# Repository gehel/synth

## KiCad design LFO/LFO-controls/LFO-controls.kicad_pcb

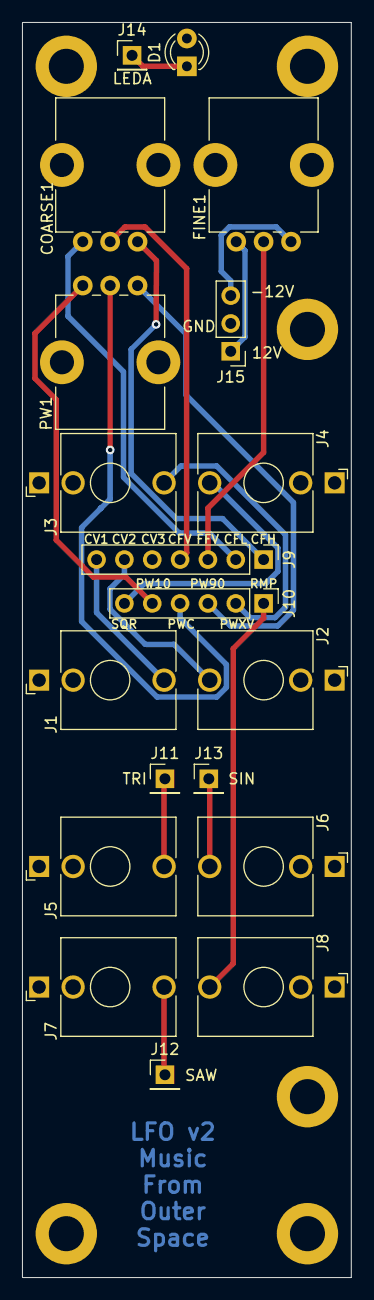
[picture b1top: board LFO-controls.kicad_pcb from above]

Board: 2 copper layers, 30.0 x 114.5 mm, 25 parts (0 on the bottom side), 19 nets.

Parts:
COARSE1: R_Potentiometer; Potentiometer_Bourns_PTV09A-1_Single_Vertical
D1: LED; LED_D3.0mm
FINE1: R_Potentiometer; Potentiometer_Bourns_PTV09A-1_Single_Vertical
H1, H2, H3, H4, H5, H6: MountingHole_Pad; MountingHole_3.2mm_M3_DIN965_Pad
J1, J2, J3, J4, J5, J6, J7, J8: AudioJack2; Jack_3.5mm_QingPu_WQP-PJ398SM_Vertical_CircularHoles
J9: Conn_01x06; PinHeader_1x07_P2.54mm_Vertical
J10: Conn_01x06; PinHeader_1x06_P2.54mm_Vertical
J11, J12, J13, J14: Conn_01x01; PinHeader_1x01_P2.54mm_Vertical
J15: Conn_01x03; PinHeader_1x03_P2.54mm_Vertical
PW1: R_Potentiometer; Potentiometer_Bourns_PTV09A-1_Single_Vertical

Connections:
+12V: FINE1.3, J15.1
-12V: FINE1.1, J15.3
CFH: COARSE1.1, J9.1
CFL: COARSE1.3, J9.2
CFV: COARSE1.2, J9.4
CV1: J1.T, J9.7
CV2: J2.T, J9.6
FFV: FINE1.2, J9.3
GND: D1.2 (A), H1.1, H2.1, H3.1, H4.1, H5.1, H6.1, J1.S, J2.S, J3.S, J4.S, J5.S, J6.S, J7.S, J8.S, J15.2
LEDA: D1.1 (K), J14.1
PW10: J10.5, PW1.1
PW90: J10.3, PW1.3
PWC: J10.4, PW1.2
PWXV: J3.T, J10.2
RMP: J8.T, J10.1
SAW: J7.T, J12.1
SIN: J6.T, J13.1
SQR: J4.T, J10.6
TRI: J5.T, J11.1

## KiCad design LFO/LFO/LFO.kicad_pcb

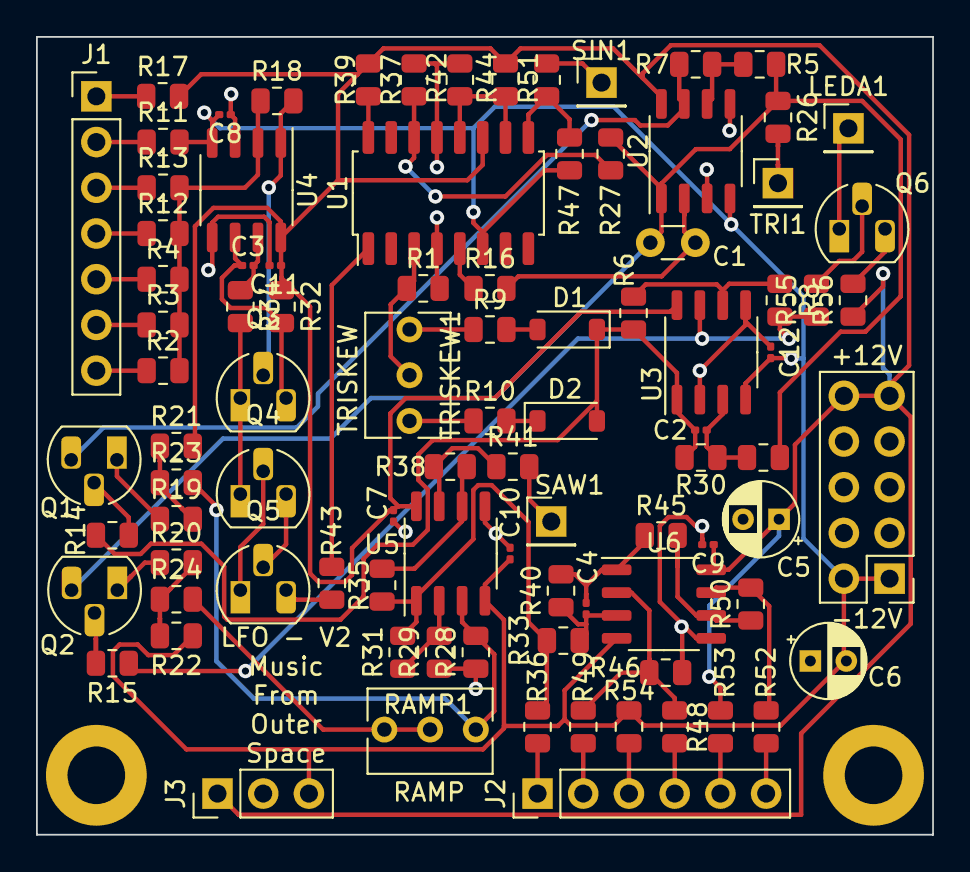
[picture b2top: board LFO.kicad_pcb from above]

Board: 2 copper layers, 49.8 x 44.3 mm, 94 parts (0 on the bottom side), 65 nets.

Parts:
C1: 20nF; C_Disc_D3.0mm_W1.6mm_P2.50mm
C2, C4: 10pF; C_0201_0603Metric
C3: 100pF; C_0201_0603Metric
C5, C6: 10uF; CP_Radial_D4.0mm_P2.00mm
C7, C8, C9, C10, C11, C12: 100nF; C_0201_0603Metric
D1, D2: 1N914; D_SOD-123
H1, H2: MountingHole_Pad; MountingHole_3.2mm_M3_DIN965_Pad
J1: Conn_01x06; PinHeader_1x07_P2.54mm_Vertical
J2: Conn_01x06; PinHeader_1x06_P2.54mm_Vertical
J3: Conn_01x03; PinHeader_1x03_P2.54mm_Vertical
J4: Conn_02x05_Odd_Even; PinHeader_2x05_P2.54mm_Vertical
LEDA1: Conn_01x01; PinHeader_1x01_P2.54mm_Vertical
Q1, Q2: NJFET; TO-92_HandSolder
Q3, Q4, Q6: 2N3904; TO-92_HandSolder
Q5: 2N3906; TO-92_HandSolder
R1, R36, R41: 1K; R_0805_2012Metric
R2, R3, R4, R9, R10, R12, R26, R31, R33, R53, R54, R55: 100K; R_0805_2012Metric
R5, R7: 20K; R_0805_2012Metric
R6, R8, R29: 47K; R_0805_2012Metric
R11, R18, R32, R47, R51, R56: 4.7K; R_0805_2012Metric
R13: 3M; R_0805_2012Metric
R14, R15: 30K; R_0805_2012Metric
R16: 39K; R_0805_2012Metric
R17, R45: 27K; R_0805_2012Metric
R19, R20, R23, R28, R34, R35, R38, R43, R48, R49, R50, R52: 10K; R_0805_2012Metric
R21, R22: 15K; R_0805_2012Metric
R24: 9.1K; R_0805_2012Metric
R25: 120K; R_0805_2012Metric
R27: 110K; R_0805_2012Metric
R30: 270K; R_0805_2012Metric
R37: 2K; R_0805_2012Metric
R39, R42: 180K; R_0805_2012Metric
R40: 4.7M; R_0805_2012Metric
R44: 2M; R_0805_2012Metric
R46: 1M; R_0805_2012Metric
RAMP1: 2K; Potentiometer_Bourns_3266Y_Vertical
SAW1: Conn_01x01; PinHeader_1x01_P2.54mm_Vertical
SIN1: Conn_01x01; PinHeader_1x01_P2.54mm_Vertical
TRI1: Conn_01x01; PinHeader_1x01_P2.54mm_Vertical
TRISKEW1: 100K; Potentiometer_Bourns_3266Y_Vertical
U1: LM13700; SOP-16_4.4x10.4mm_P1.27mm
U2, U3, U5, U6: TL082; SOP-8_3.9x4.9mm_P1.27mm
U4: TL072; SOP-8_3.9x4.9mm_P1.27mm

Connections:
+12V: C5.1, C7.1, C9.1, C11.1, J3.1, J4.9, J4.10, R17.2, R21.2, R32.1, R39.1, R44.2, R53.1, R56.1, U1.11 (V+), U2.8 (V+), U3.8 (V+), U4.8 (V+), U5.8 (V+), U6.8 (V+)
-12V: C6.2, C8.2, C10.2, C12.2, J3.3, J4.1, J4.2, R11.2, R22.1, R47.2, R54.2, U1.6 (V-), U2.4 (V-), U3.4 (V-), U4.4 (V-), U5.4 (V-), U6.4 (V-)
CFH: J1.1, R17.1
CFL: J1.2, R11.1
CFV: J1.4, R12.1
CV1: J1.7, R2.1
CV2: J1.6, R3.1
CV3: J1.5, R4.1
FFV: J1.3, R13.1
GND: C5.2, C6.1, C7.2, C8.1, C9.2, C10.1, C11.2, C12.1, H1.1, H2.1, J3.2, J4.3, J4.4, J4.5, J4.6, J4.7, J4.8, Q4.2 (B), Q5.1 (E), R1.2, R28.1, R29.1, R37.1, R42.1, R46.1, U1.4 (-), U1.13 (-), U2.3 (+), U2.5 (+), U3.2 (-), U3.5 (+), U4.3 (+), U4.5 (+), U5.5 (+), U6.5 (+)
LEDA: LEDA1.1, Q6.1 (E)
unnamed: C3.2, R34.1, U4.7
unnamed: C4.2, R40.2, R45.1, U6.1
unnamed: D1.2 (A), R9.2
unnamed: C2.2, D1.1 (K), D2.2 (A), R6.1, R14.1, R30.2, U3.1
unnamed: D2.1 (K), R10.2
unnamed: Q1.1 (D), R19.1
unnamed: Q1.2 (G), R14.2
unnamed: Q1.3 (S), R7.2, U2.7
unnamed: Q2.1 (D), R20.1
unnamed: Q2.2 (G), R15.2
unnamed: C1.2, Q2.3 (S), R5.1, R25.1, R26.1, R27.1, U2.1
unnamed: Q3.2 (B), R18.2, U4.1
unnamed: C3.1, Q3.3 (C), R32.2, U4.6 (-)
unnamed: Q3.1 (E), Q4.1 (E), R34.2
unnamed: Q4.3 (C), Q5.2 (B)
unnamed: Q5.3 (C), R43.1
unnamed: Q6.2 (B), R55.2
unnamed: Q6.3 (C), R56.2
unnamed: R9.1, TRISKEW1.3
unnamed: R10.1, TRISKEW1.1
unnamed: R16.1, U1.5
unnamed: R19.2, R21.1, R23.1
unnamed: R20.2, R22.2, R24.1
unnamed: R24.2, RAMP1.2, RAMP1.3
unnamed: R31.2, R33.1, R35.1, R36.1, U5.1
unnamed: R38.2, R41.1, U5.7
unnamed: R39.2, U1.16
unnamed: R42.2, R44.1, U1.10, U1.12
unnamed: R43.2, U1.1
unnamed: R47.1, R51.1, U1.9
unnamed: R50.2, R52.1, U6.7
unnamed: R27.2, R37.2, U1.14 (+)
unnamed: R1.1, TRISKEW1.2, U1.3 (+)
unnamed: C1.1, R16.2, U2.2 (-)
unnamed: R5.2, R7.1, U2.6 (-)
unnamed: C2.1, R25.2, R30.1, U3.3 (+)
unnamed: R6.2, R8.1, U3.6 (-)
unnamed: R2.2, R3.2, R4.2, R12.2, R13.2, R18.1, U4.2 (-)
unnamed: R23.2, R28.2, RAMP1.1, U5.3 (+)
unnamed: R29.2, R31.1, U5.2 (-)
unnamed: R35.2, R38.1, U5.6 (-)
unnamed: C4.1, R33.2, R40.1, U6.3 (+)
unnamed: R46.2, R48.1, R49.1, U6.2 (-)
unnamed: R45.2, R50.1, U6.6 (-)
PW10: J2.5, R53.2
PW90: J2.3, R54.1
PWC: J2.4, R48.2
PWXV: J2.2, R49.2
RMP: J2.1, R36.2
SAW: R41.2, SAW1.1
SIN: R51.2, SIN1.1
SQR: J2.6, R52.2
TRI: R26.2, TRI1.1
ZZ: R8.2, R15.1, R55.1, U3.7

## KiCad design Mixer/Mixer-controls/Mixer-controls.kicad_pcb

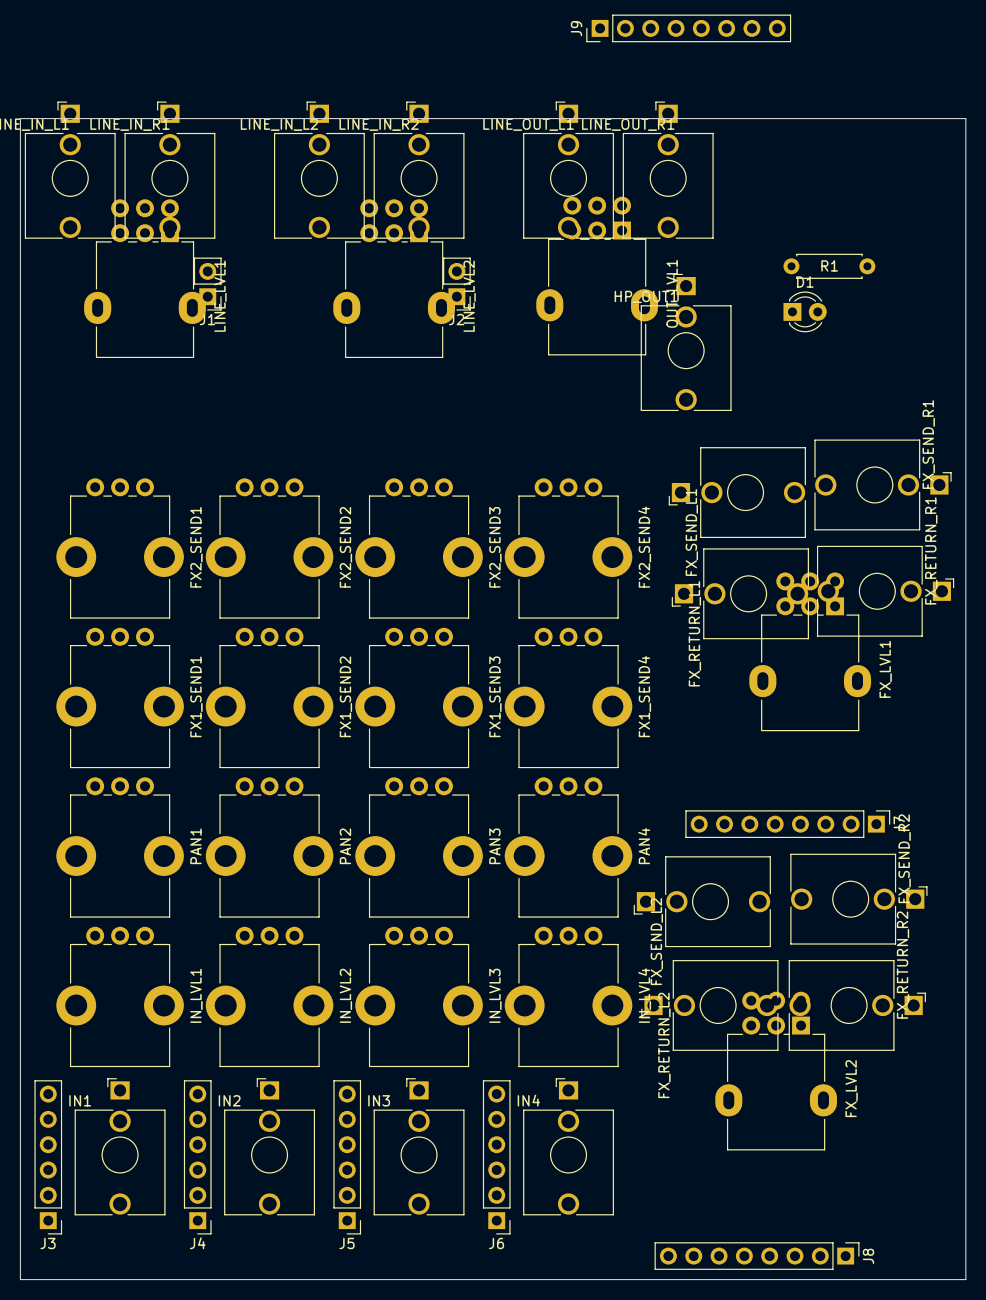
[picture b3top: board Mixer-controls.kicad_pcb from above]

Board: 2 copper layers, 94.9 x 116.5 mm, 51 parts (0 on the bottom side), 45 nets, no tracks yet.

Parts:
D1: LED; LED_D3.0mm
FX1_SEND1, FX1_SEND2, FX1_SEND3, FX1_SEND4, FX2_SEND1, FX2_SEND2, FX2_SEND3, FX2_SEND4: 100K; Potentiometer_Bourns_PTV09A-1_Single_Vertical
FX_LVL1, FX_LVL2: 100K; Potentiometer_Alpha_RD902F-40-00D_Dual_Vertical
FX_RETURN_L1, FX_RETURN_L2: AudioJack3; Jack_3.5mm_QingPu_WQP-PJ398SM_Vertical_CircularHoles
FX_RETURN_R1, FX_RETURN_R2: AudioJack3; Jack_3.5mm_QingPu_WQP-PJ398SM_Vertical_CircularHoles
FX_SEND_L1, FX_SEND_L2: AudioJack3; Jack_3.5mm_QingPu_WQP-PJ398SM_Vertical_CircularHoles
FX_SEND_R1, FX_SEND_R2: AudioJack3; Jack_3.5mm_QingPu_WQP-PJ398SM_Vertical_CircularHoles
HP_OUT1: AudioJack3; Jack_3.5mm_QingPu_WQP-PJ398SM_Vertical_CircularHoles
IN1, IN2, IN3, IN4: AudioJack3; Jack_3.5mm_QingPu_WQP-PJ398SM_Vertical_CircularHoles
IN_LVL1, IN_LVL2, IN_LVL3, IN_LVL4: 100K; Potentiometer_Bourns_PTV09A-1_Single_Vertical
J1, J2: Conn_01x02; PinHeader_1x02_P2.54mm_Vertical
J3, J4, J5, J6: Conn_01x06; PinHeader_1x06_P2.54mm_Vertical
J7, J8, J9: Conn_01x08; PinHeader_1x08_P2.54mm_Vertical
LINE_IN_L1, LINE_IN_L2: AudioJack3; Jack_3.5mm_QingPu_WQP-PJ398SM_Vertical_CircularHoles
LINE_IN_R1, LINE_IN_R2: AudioJack3; Jack_3.5mm_QingPu_WQP-PJ398SM_Vertical_CircularHoles
LINE_LVL1, LINE_LVL2: 100K; Potentiometer_Alpha_RD902F-40-00D_Dual_Vertical
LINE_OUT_L1: AudioJack3; Jack_3.5mm_QingPu_WQP-PJ398SM_Vertical_CircularHoles
LINE_OUT_R1: AudioJack3; Jack_3.5mm_QingPu_WQP-PJ398SM_Vertical_CircularHoles
OUT_LVL1: 100K; Potentiometer_Alpha_RD902F-40-00D_Dual_Vertical
PAN1, PAN2, PAN3, PAN4: 100K; Potentiometer_Bourns_PTV09A-1_Single_Vertical
R1: 4.7K; R_Axial_DIN0207_L6.3mm_D2.5mm_P7.62mm_Horizontal

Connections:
/channel1/E1: FX1_SEND1.2, J3.5
/channel1/E2: FX2_SEND1.2, J3.6
/channel1/EF: FX1_SEND1.3, FX2_SEND1.3, J3.4
/channel1/IN: IN_LVL1.2, J3.1
/channel1/PANL: J3.2, PAN1.1
/channel1/PANR: J3.3, PAN1.3
/channel2/E1: FX1_SEND2.2, J4.5
/channel2/E2: FX2_SEND2.2, J4.6
/channel2/EF: FX1_SEND2.3, FX2_SEND2.3, J4.4
/channel2/IN: IN_LVL2.2, J4.1
/channel2/PANL: J4.2, PAN2.1
/channel2/PANR: J4.3, PAN2.3
/channel3/E1: FX1_SEND3.2, J5.5
/channel3/E2: FX2_SEND3.2, J5.6
/channel3/EF: FX1_SEND3.3, FX2_SEND3.3, J5.4
/channel3/IN: IN_LVL3.2, J5.1
/channel3/PANL: J5.2, PAN3.1
/channel3/PANR: J5.3, PAN3.3
/channel4/E1: FX1_SEND4.2, J6.5
/channel4/E2: FX2_SEND4.2, J6.6
/channel4/EF: FX1_SEND4.3, FX2_SEND4.3, J6.4
/channel4/IN: IN_LVL4.2, J6.1
/channel4/PANL: J6.2, PAN4.1
/channel4/PANR: J6.3, PAN4.3
/outputs/HPHR: HP_OUT1.T, J9.7
/outputs/HPIL: J9.1, OUT_LVL1.2
/outputs/HPIR: J9.8, OUT_LVL1.5
/outputs/HPOL: J9.3, OUT_LVL1.3
/outputs/HPOR: J9.6, OUT_LVL1.6
/outputs/LLOUT: J9.4, LINE_OUT_R1.T
/outputs/RLOUT: J9.5, LINE_OUT_L1.T
GND: FX1_SEND1.1, FX1_SEND1.MP (MountPin), FX1_SEND2.1, FX1_SEND2.MP (MountPin), FX1_SEND3.1, FX1_SEND3.MP (MountPin), FX1_SEND4.1, FX1_SEND4.MP (MountPin), FX2_SEND1.1, FX2_SEND1.MP (MountPin), FX2_SEND2.1, FX2_SEND2.MP (MountPin), FX2_SEND3.1, FX2_SEND3.MP (MountPin), FX2_SEND4.1, FX2_SEND4.MP (MountPin), FX_RETURN_L1.S, FX_RETURN_L2.S, FX_RETURN_R1.S, FX_RETURN_R2.S, FX_SEND_L1.S, FX_SEND_L2.S, FX_SEND_R1.S, FX_SEND_R2.S, HP_OUT1.S, IN1.S, IN2.S, IN3.S, IN4.S, IN_LVL1.1, IN_LVL1.MP (MountPin), IN_LVL2.1, IN_LVL2.MP (MountPin), IN_LVL3.1, IN_LVL3.MP (MountPin), IN_LVL4.1, IN_LVL4.MP (MountPin), LINE_IN_L1.S, LINE_IN_L2.S, LINE_IN_R1.S, LINE_IN_R2.S, LINE_LVL1.1, LINE_LVL1.4, LINE_LVL2.1, LINE_LVL2.4, LINE_OUT_L1.S, LINE_OUT_R1.S, OUT_LVL1.1, OUT_LVL1.4, PAN1.2, PAN1.MP (MountPin), PAN2.2, PAN2.MP (MountPin), PAN3.2, PAN3.MP (MountPin), PAN4.2, PAN4.MP (MountPin), R1.2
unnamed: D1.1 (K), R1.1
unnamed: IN1.T, IN_LVL1.3
unnamed: IN2.T, IN_LVL2.3
unnamed: IN3.T, IN_LVL3.3
unnamed: IN4.T, IN_LVL4.3
unnamed: J1.1, LINE_LVL1.2
unnamed: J1.2, LINE_LVL1.5
unnamed: J2.1, LINE_LVL2.2
unnamed: J2.2, LINE_LVL2.5
unnamed: LINE_IN_L1.T, LINE_LVL1.3
unnamed: LINE_IN_L2.T, LINE_LVL2.3
unnamed: LINE_IN_R1.T, LINE_LVL1.6
unnamed: LINE_IN_R2.T, LINE_LVL2.6

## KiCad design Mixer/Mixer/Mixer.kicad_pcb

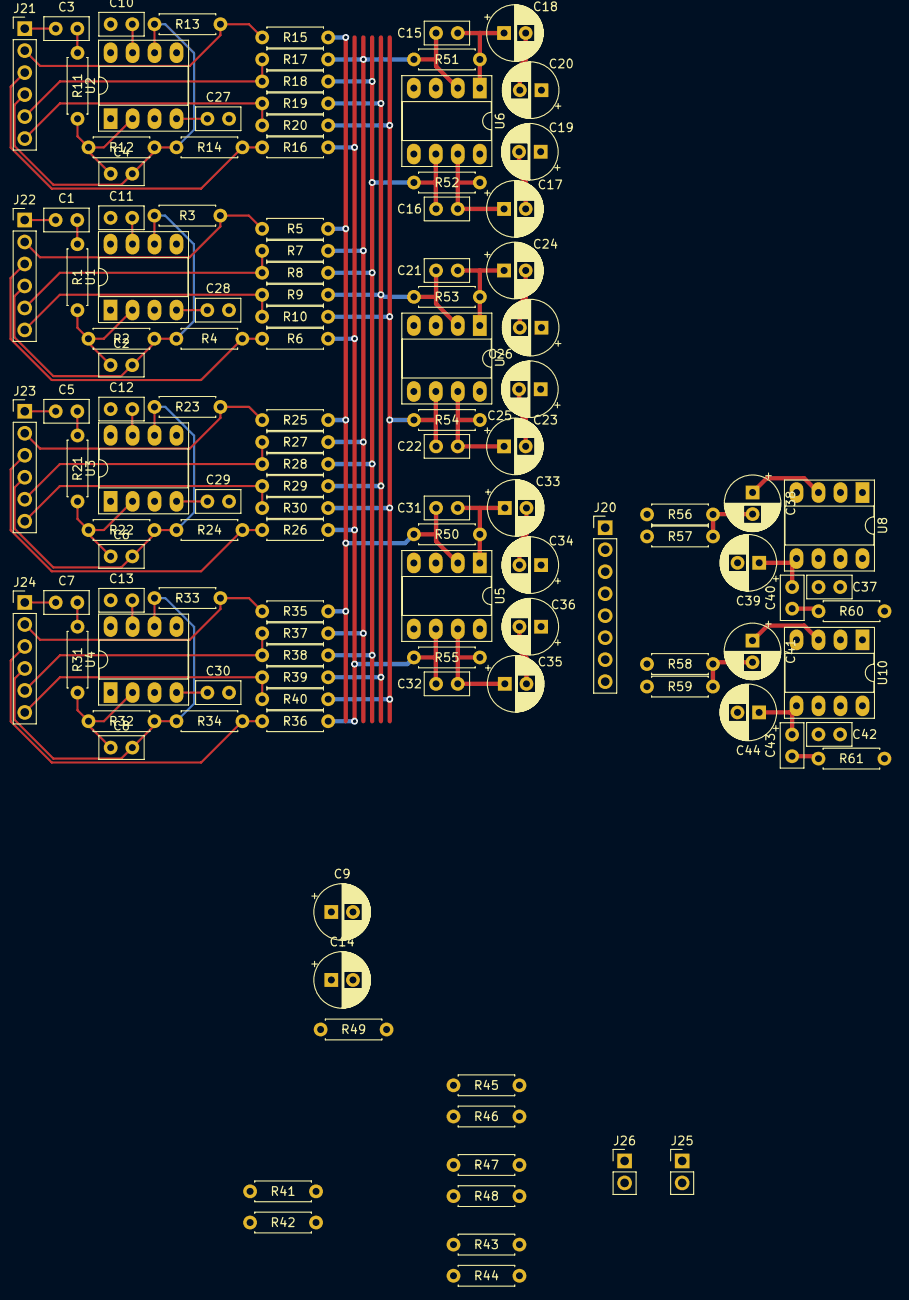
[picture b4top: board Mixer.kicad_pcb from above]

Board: 2 copper layers, 121 parts (0 on the bottom side), 71 nets.

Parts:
C1, C3, C5, C7, C10, C11, C12, C13, C27, C28, C29, C30, C37, C42: 100nF; C_Disc_D5.0mm_W2.5mm_P2.50mm
C2, C4, C6, C8, C15, C16, C21, C22, C31, C32: 10pF; C_Disc_D5.0mm_W2.5mm_P2.50mm
C9, C14: 10uF; CP_Radial_D6.3mm_P2.50mm
C17, C18, C19, C20, C23, C24, C25, C26, C33, C34, C35, C36: 47uF; CP_Radial_D6.3mm_P2.50mm
C38, C41: 1uF; CP_Radial_D6.3mm_P2.50mm
C39, C44: 220uF; CP_Radial_D6.3mm_P2.50mm
C40, C43: 47nF; C_Disc_D5.0mm_W2.5mm_P2.50mm
J20: Conn_01x08; PinHeader_1x08_P2.54mm_Vertical
J21, J22, J23, J24: Conn_01x06; PinHeader_1x06_P2.54mm_Vertical
J25, J26: Conn_01x02; PinHeader_1x02_P2.54mm_Vertical
R1, R11, R21, R31: 47K; R_Axial_DIN0207_L6.3mm_D2.5mm_P7.62mm_Horizontal
R2, R12, R22, R32: 470K; R_Axial_DIN0207_L6.3mm_D2.5mm_P7.62mm_Horizontal
R3, R4, R5, R6, R13, R14, R15, R16, R23, R24, R25, R26, R33, R34, R35, R36, R49: 120K; R_Axial_DIN0207_L6.3mm_D2.5mm_P7.62mm_Horizontal
R7, R8, R9, R10, R17, R18, R19, R20, R27, R28, R29, R30, R37, R38, R39, R40: 20K; R_Axial_DIN0207_L6.3mm_D2.5mm_P7.62mm_Horizontal
R41, R42, R43, R44, R45, R46, R47, R48: 150K; R_Axial_DIN0207_L6.3mm_D2.5mm_P7.62mm_Horizontal
R50, R55: 300K; R_Axial_DIN0207_L6.3mm_D2.5mm_P7.62mm_Horizontal
R51, R52, R53, R54: 15K; R_Axial_DIN0207_L6.3mm_D2.5mm_P7.62mm_Horizontal
R56, R58: 100K; R_Axial_DIN0207_L6.3mm_D2.5mm_P7.62mm_Horizontal
R57, R59: 4.7K; R_Axial_DIN0207_L6.3mm_D2.5mm_P7.62mm_Horizontal
R60, R61: 10R; R_Axial_DIN0207_L6.3mm_D2.5mm_P7.62mm_Horizontal
U1, U2, U3, U4: TL071; DIP-8_W7.62mm_Socket_LongPads
U5, U6, U7: TL072; DIP-8_W7.62mm_Socket_LongPads
U8, U10: LM386; DIP-8_W7.62mm_Socket_LongPads

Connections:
+12V: C9.1, C10.2, C11.2, C12.2, C13.2, C37.2, C42.2, U1.7 (V+), U2.7 (V+), U3.7 (V+), U4.7 (V+), U5.8 (V+), U6.8 (V+), U7.8 (V+), U8.6 (V+), U10.6 (V+)
-12V: C14.2, C27.1, C28.1, C29.1, C30.1, U1.4 (V-), U2.4 (V-), U3.4 (V-), U4.4 (V-), U5.4 (V-), U6.4 (V-), U7.4 (V-)
C1E1: J21.5, R17.1, R18.1
C1E2: J21.6, R19.1, R20.1
C2E1: J22.5, R7.1, R8.1
C2E2: J22.6, R9.1, R10.1
C3E1: J23.5, R27.1, R28.1
C3E2: J23.6, R29.1, R30.1
C4E1: J24.5, R37.1, R38.1
C4E2: J24.6, R39.1, R40.1
E1LB: C15.1, R7.2, R17.2, R27.2, R37.2, R51.1, U6.2 (-)
E1RB: C16.1, R8.2, R18.2, R28.2, R38.2, R52.1, U6.6 (-)
E2LB: C21.1, R9.2, R19.2, R29.2, R39.2, R53.1, U7.2 (-)
E2RB: C22.1, R10.2, R20.2, R30.2, R40.2, R54.1, U7.6 (-)
EFCH1: C4.2, J21.4, R12.2, R13.1, R14.1, U2.6
EFCH2: C2.2, J22.4, R2.2, R3.1, R4.1, U1.6
EFCH3: C6.2, J23.4, R22.2, R23.1, R24.1, U3.6
EFCH4: C8.2, J24.4, R32.2, R33.1, R34.1, U4.6
GND: C9.2, C10.1, C11.1, C12.1, C13.1, C14.1, C27.2, C28.2, C29.2, C30.2, C37.1, C42.1, R49.1, R57.1, R59.1, R60.2, R61.2, U1.3 (+), U2.3 (+), U3.3 (+), U4.3 (+), U5.3 (+), U5.5 (+), U6.3 (+), U6.5 (+), U7.3 (+), U7.5 (+), U8.2 (-), U8.4 (GND), U10.2 (-), U10.4 (GND)
HPHL: C39.2, J20.2
HPHR: C44.2, J20.7
HPIL: J20.1, R56.1
HPIR: J20.8, R58.1
HPOL: C31.2, C33.1, J20.3, R50.2, U5.1
HPOR: C32.2, C35.1, J20.6, R55.2, U5.7
IN1: C3.1, J21.1
IN2: C1.1, J22.1
IN3: C5.1, J23.1
IN4: C7.1, J24.1
LAB: C31.1, R5.2, R15.2, R25.2, R35.2, R41.2, R43.2, R45.2, R47.2, R50.1, U5.2 (-)
LLOUT: C34.1, J20.4
unnamed: C1.2, R1.1
unnamed: C3.2, R11.1
unnamed: C5.2, R21.1
unnamed: C7.2, R31.1
unnamed: C15.2, C18.1, R51.2, U6.1
unnamed: C16.2, C17.1, R52.2, U6.7
unnamed: C17.2, C19.2
unnamed: C18.2, C20.2
unnamed: C21.2, C24.1, R53.2, U7.1
unnamed: C22.2, C23.1, R54.2, U7.7
unnamed: C23.2, C25.2
unnamed: C24.2, C26.2
unnamed: C33.2, C34.2
unnamed: C35.2, C36.2
unnamed: C38.2, R56.2, R57.2
unnamed: C39.1, C40.2, U8.5
unnamed: C40.1, R60.1
unnamed: C41.2, R58.2, R59.2
unnamed: C43.1, R61.1
unnamed: C43.2, C44.1, U10.5
unnamed: C2.1, R1.2, R2.1, U1.2 (-)
unnamed: C4.1, R11.2, R12.1, U2.2 (-)
unnamed: C6.1, R21.2, R22.1, U3.2 (-)
unnamed: C8.1, R31.2, R32.1, U4.2 (-)
unnamed: C38.1, U8.3 (+)
unnamed: C41.1, U10.3 (+)
PAN1L: J21.2, R13.2, R15.1
PAN1R: J21.3, R14.2, R16.1
PAN2L: J22.2, R3.2, R5.1
PAN2R: J22.3, R4.2, R6.1
PAN3L: J23.2, R23.2, R25.1
PAN3R: J23.3, R24.2, R26.1
PAN4L: J24.2, R33.2, R35.1
PAN4R: J24.3, R34.2, R36.1
RAB: C32.1, R6.2, R16.2, R26.2, R36.2, R42.2, R44.2, R46.2, R48.2, R55.1, U5.6 (-)
RLOUT: C36.1, J20.5
SL1L: J25.1, R47.1
SL1R: J25.2, R48.1
SL2L: J26.1, R45.1
SL2R: J26.2, R46.1

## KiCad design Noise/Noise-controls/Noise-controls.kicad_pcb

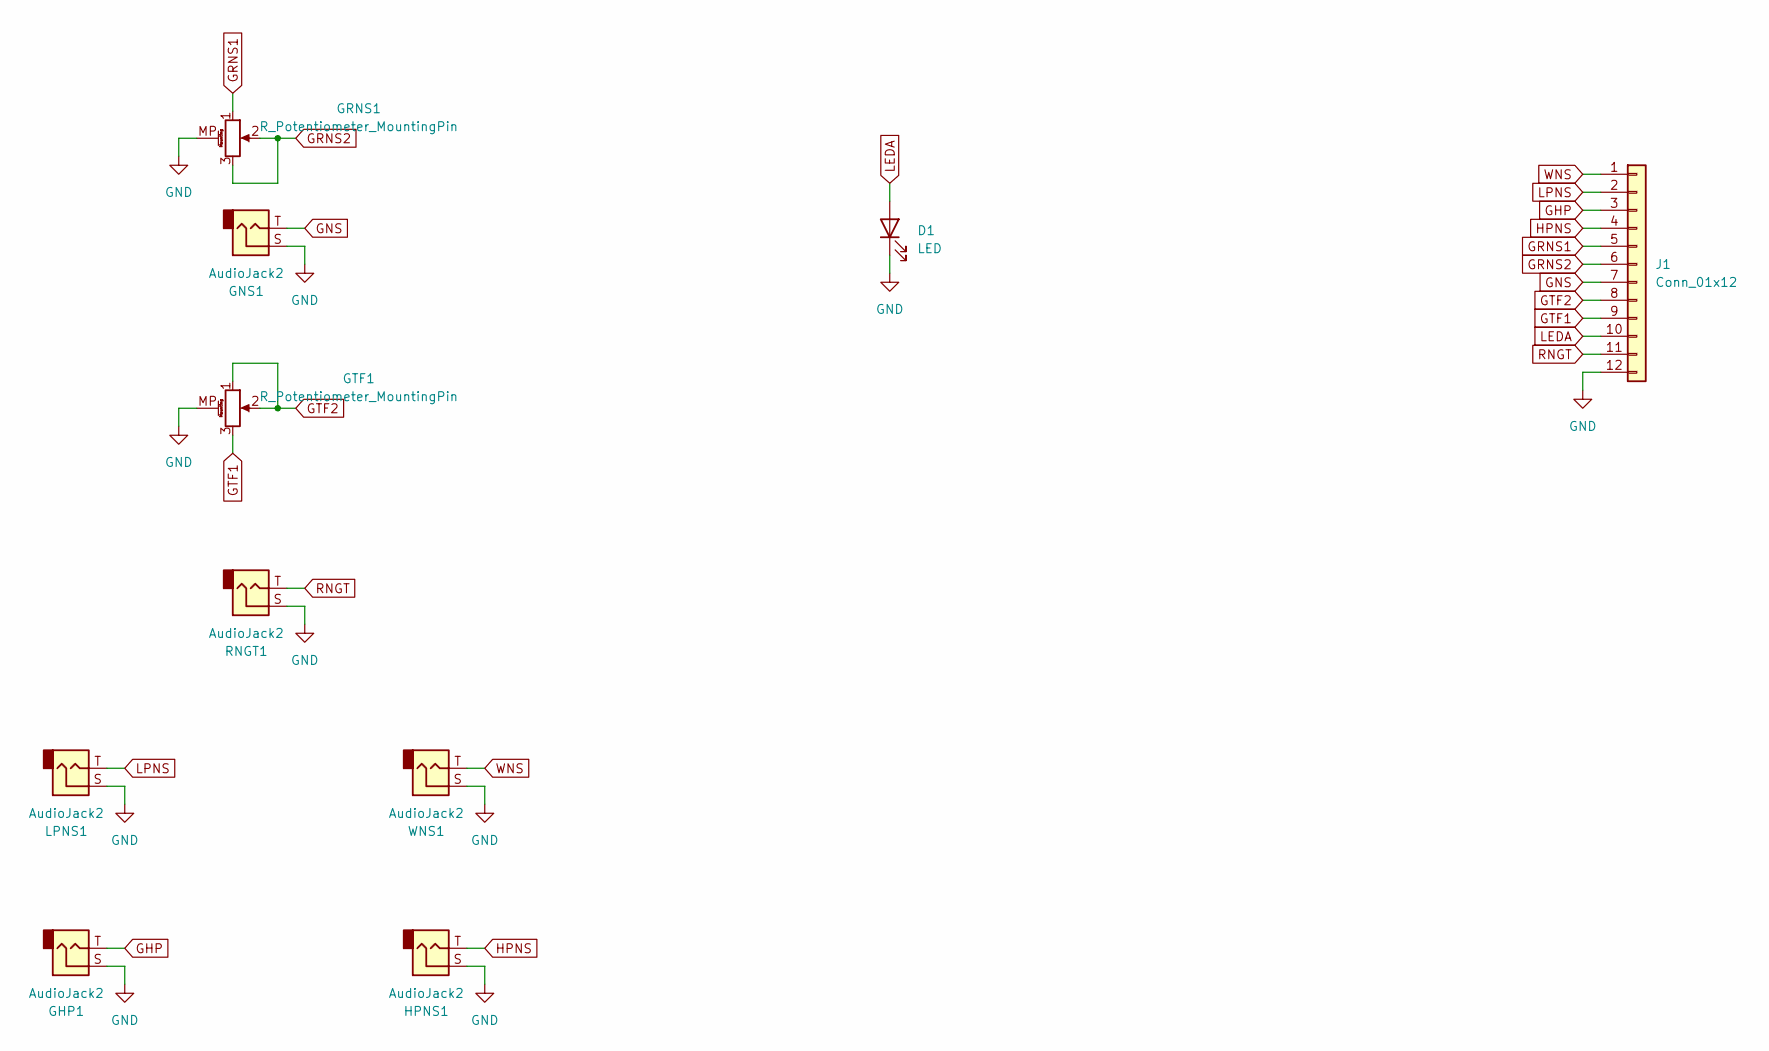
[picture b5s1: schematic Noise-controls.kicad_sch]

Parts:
D1: LED; LED_D3.0mm
GHP1: AudioJack2; Jack_3.5mm_QingPu_WQP-PJ398SM_Vertical_CircularHoles
GNS1: AudioJack2; Jack_3.5mm_QingPu_WQP-PJ398SM_Vertical_CircularHoles
GRNS1: R_Potentiometer_MountingPin; Potentiometer_Bourns_PTV09A-1_Single_Vertical
GTF1: R_Potentiometer_MountingPin; Potentiometer_Bourns_PTV09A-1_Single_Vertical
HPNS1: AudioJack2; Jack_3.5mm_QingPu_WQP-PJ398SM_Vertical_CircularHoles
J1: Conn_01x12; PinHeader_1x12_P2.54mm_Vertical
LPNS1: AudioJack2; Jack_3.5mm_QingPu_WQP-PJ398SM_Vertical_CircularHoles
RNGT1: AudioJack2; Jack_3.5mm_QingPu_WQP-PJ398SM_Vertical_CircularHoles
WNS1: AudioJack2; Jack_3.5mm_QingPu_WQP-PJ398SM_Vertical_CircularHoles

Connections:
GHP: GHP1.T, J1.3
GND: D1.1 (K), GHP1.S, GNS1.S, GRNS1.MP (MountPin), GTF1.MP (MountPin), HPNS1.S, J1.12, LPNS1.S, RNGT1.S, WNS1.S
GNS: GNS1.T, J1.7
GRNS1: GRNS1.1, J1.5
GRNS2: GRNS1.2, GRNS1.3, J1.6
GTF1: GTF1.3, J1.9
GTF2: GTF1.1, GTF1.2, J1.8
HPNS: HPNS1.T, J1.4
LEDA: D1.2 (A), J1.10
LPNS: J1.2, LPNS1.T
RNGT: J1.11, RNGT1.T
WNS: J1.1, WNS1.T

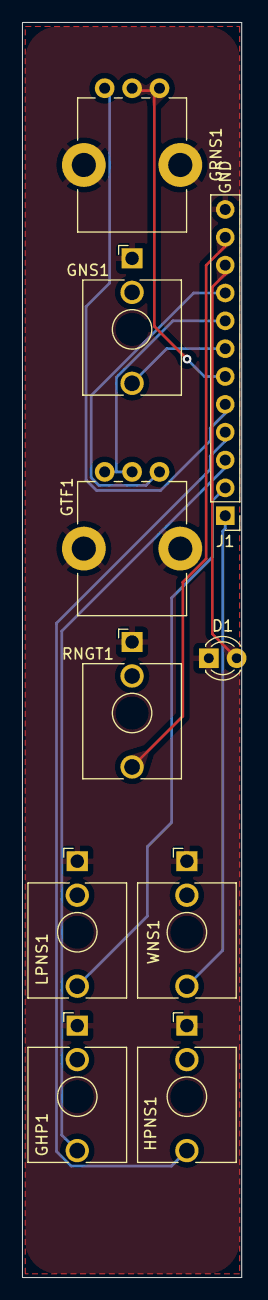
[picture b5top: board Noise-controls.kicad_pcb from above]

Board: 2 copper layers, 20.0 x 114.5 mm, 10 parts (0 on the bottom side), 12 nets.

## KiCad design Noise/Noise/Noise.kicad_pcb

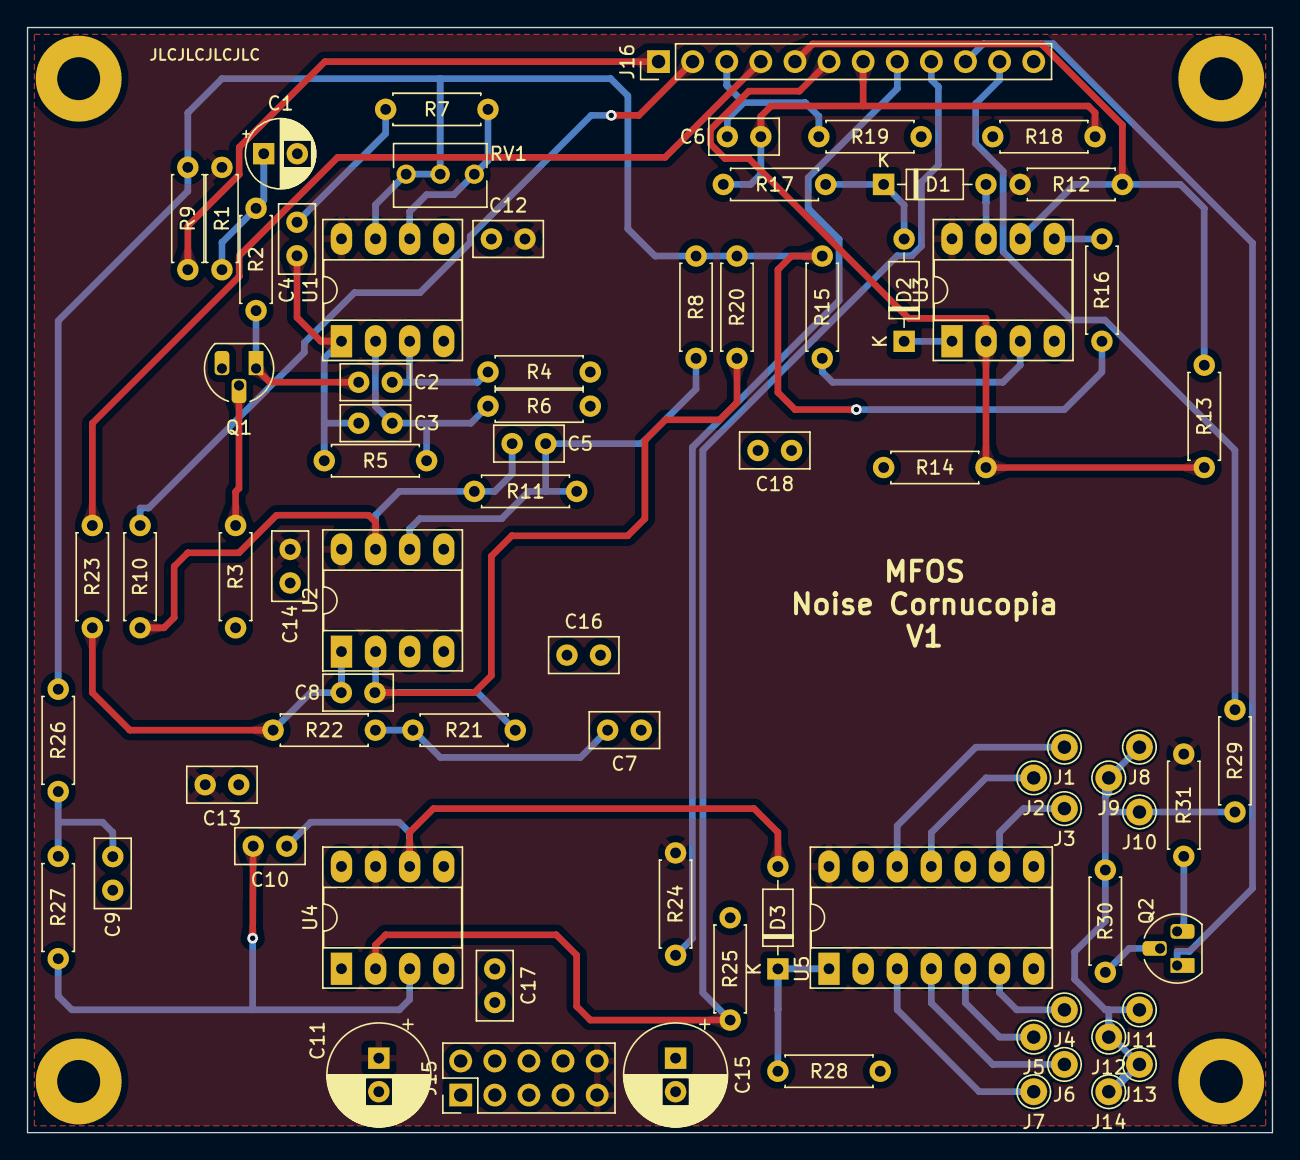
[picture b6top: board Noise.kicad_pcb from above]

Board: 4 copper layers, 92.7 x 82.3 mm, 80 parts (0 on the bottom side), 47 nets.

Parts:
C1: 1uF; CP_Radial_D5.0mm_P2.50mm
C2, C4, C12, C13, C14, C16, C17, C18: 100nF; C_Disc_D5.0mm_W2.5mm_P2.50mm
C3, C10: 10pF; C_Disc_D5.0mm_W2.5mm_P2.50mm
C5, C6: 1nF; C_Disc_D5.0mm_W2.5mm_P2.50mm
C7: 10nF; C_Disc_D5.0mm_W2.5mm_P2.50mm
C8: 100pF; C_Disc_D5.0mm_W2.5mm_P2.50mm
C9: 4.7nF; C_Disc_D5.0mm_W2.5mm_P2.50mm
C11, C15: 1uF; CP_Radial_D7.5mm_P2.50mm
D1, D2, D3: 1N914; D_DO-35_SOD27_P7.62mm_Horizontal
H1, H2, H3, H4: MountingHole_Pad; MountingHole_3.2mm_M3_Pad
J1, J2, J3, J4, J5, J6, J7, J8, J9, J10, J11, J12, J13, J14: Conn_01x01_Male; Pin_D1.0mm_L10.0mm
J15: Conn_02x05_Odd_Even; PinHeader_2x05_P2.54mm_Vertical
J16: Conn_01x12; PinHeader_1x12_P2.54mm_Vertical
Q1, Q2: 2N3904; TO-92_HandSolder
R1, R2, R5, R20: 470K; R_Axial_DIN0207_L6.3mm_D2.5mm_P7.62mm_Horizontal
R3, R6, R7, R15, R16: 10K; R_Axial_DIN0207_L6.3mm_D2.5mm_P7.62mm_Horizontal
R4: 2M; R_Axial_DIN0207_L6.3mm_D2.5mm_P7.62mm_Horizontal
R8: 100K; R_Axial_DIN0207_L6.3mm_D2.5mm_P7.62mm_Horizontal
R9, R10, R23, R29: 1K; R_Axial_DIN0207_L6.3mm_D2.5mm_P7.62mm_Horizontal
R11: 1M; R_Axial_DIN0207_L6.3mm_D2.5mm_P7.62mm_Horizontal
R12, R14, R24, R30: 47K; R_Axial_DIN0207_L6.3mm_D2.5mm_P7.62mm_Horizontal
R13: 200K; R_Axial_DIN0207_L6.3mm_D2.5mm_P7.62mm_Horizontal
R17, R18, R19, R31: 4.7K; R_Axial_DIN0207_L6.3mm_D2.5mm_P7.62mm_Horizontal
R21, R22: 43K; R_Axial_DIN0207_L6.3mm_D2.5mm_P7.62mm_Horizontal
R25, R26, R27, R28: 20K; R_Axial_DIN0207_L6.3mm_D2.5mm_P7.62mm_Horizontal
RV1: 500K; Potentiometer_Bourns_3266Y_Vertical
U1, U2, U3: TL072; DIP-8_W7.62mm_Socket_LongPads
U4: TL071; DIP-8_W7.62mm_Socket_LongPads
U5: 4024; DIP-14_W7.62mm_Socket_LongPads

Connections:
+12V: C11.1, C12.2, C13.2, C14.2, J15.9, J15.10, R1.1, R12.1, R24.1, R31.1, U1.8 (V+), U2.8 (V+), U3.8 (V+), U4.7 (V+), U5.14 (VDD)
-12V: C15.2, C16.1, C17.1, C18.1, J15.1, J15.2, R3.2, R14.2, U1.4 (V-), U2.4 (V-), U3.4 (V-), U4.4 (V-)
GHP: C6.2, J16.3, R19.1
GND: C1.2, C7.1, C9.1, C11.2, C12.1, C13.1, C14.1, C15.1, C16.2, C17.2, C18.2, H1.1, H2.1, H3.1, H4.1, J15.3, J15.4, J15.5, J15.6, J15.7, J15.8, J16.12, R4.2, R6.1, R18.2, R19.2, R25.2, R28.2, U1.5 (+), U2.3 (+), U2.5 (+), U5.2 (MR), U5.7 (VSS)
GNS: C6.1, J16.7, R17.2, R18.1
GRNS1: J16.5, R12.2, R13.1, U3.6 (-)
GRNS2: J16.6, R13.2, R14.1, U3.2 (-)
GTF1: J16.9, R25.1, U4.2 (-)
GTF2: J16.8, R24.2
HPNS: J16.4, R23.2
LEDA: J16.10, Q2.1 (E)
LPNS: J16.2, R10.2
unnamed: C1.1, R1.2, R2.1
unnamed: C3.2, C4.1, R5.2, U1.1
unnamed: C4.2, R7.1
unnamed: C5.2, R10.1, R11.2, U2.7
unnamed: C7.2, R21.2, R22.1
unnamed: C8.1, R22.2, R23.1, U2.1
unnamed: C9.2, R26.2, R27.1
unnamed: D1.2 (A), U3.7
unnamed: D1.1 (K), D2.2 (A), R17.1
unnamed: D2.1 (K), U3.1
unnamed: C10.1, D3.2 (A), U4.6
unnamed: D3.1 (K), R28.1, U5.1 (~CLK)
unnamed: J1.1, U5.12 (Q0)
unnamed: J2.1, U5.11 (Q1)
unnamed: J3.1, U5.9 (Q2)
unnamed: J4.1, U5.6 (Q3)
unnamed: J5.1, U5.5 (Q4)
unnamed: J6.1, U5.4 (Q5)
unnamed: J7.1, U5.3 (Q6)
unnamed: J8.1, J9.1, J10.1, J11.1, J12.1, J13.1, J14.1, R29.1, R30.1
unnamed: Q1.2 (B), R3.1
unnamed: C2.1, Q1.1 (E), R2.2
unnamed: Q2.2 (B), R30.2
unnamed: Q2.3 (C), R31.2
unnamed: R8.1, R9.1, R15.1, R16.1, R20.1, R26.1, RV1.2, RV1.3, U1.7
unnamed: C2.2, R4.1, U1.3 (+)
unnamed: C3.1, R5.1, R6.2, U1.2 (-)
unnamed: R7.2, RV1.1, U1.6 (-)
unnamed: C8.2, R20.2, R21.1, U2.2 (-)
unnamed: C5.1, R8.2, R11.1, U2.6 (-)
unnamed: R15.2, U3.3 (+)
unnamed: R16.2, U3.5 (+)
unnamed: C10.2, R27.2, U4.3 (+)
RNGT: J16.11, R29.2
WNS: J16.1, R9.2
